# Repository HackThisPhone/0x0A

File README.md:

# 0x0A
The 0x0A Smartphone is an open-source, open-hardware smartphone. Repairable, customizable, and fully yours, the 0x0A phone gives the power back to you! 

## Features:

- Qualcomm Octa-Core ARM Cortex A-53 64-bit CPU @ 1.8GHz (2x quad-core with 512KB L2 cache)
- Adreno 506 GPU
- 16GB eMMC + 2GB LPDDR3
- 8,000mAh LiPo battery
- HD 720x1280 LCD with 16.7M color depth
- 10MP front & rear cameras
- 5G/4G/LTE/WCDMA
- WiFi 802.11a/b/g/n/ac
- Bluetooth 4.2/3.0/2.1
- GPS/BeiDou/GLONASS
- USB-C 3.0
- Dual SIM Standby
- 3D Printed Modular Case Design
- Full Schematics, BOM, & Supplier Info (self-serve on github)
- Android 9/10 Support
- Linux Support Planned (alternative operating systems welcomed here)

### Supported Carriers:

- North America    
  - Verizon
  - AT&T
  - T-Mobile
  - Sprint

Estimated BOM Cost: <$300
MSRP: $750

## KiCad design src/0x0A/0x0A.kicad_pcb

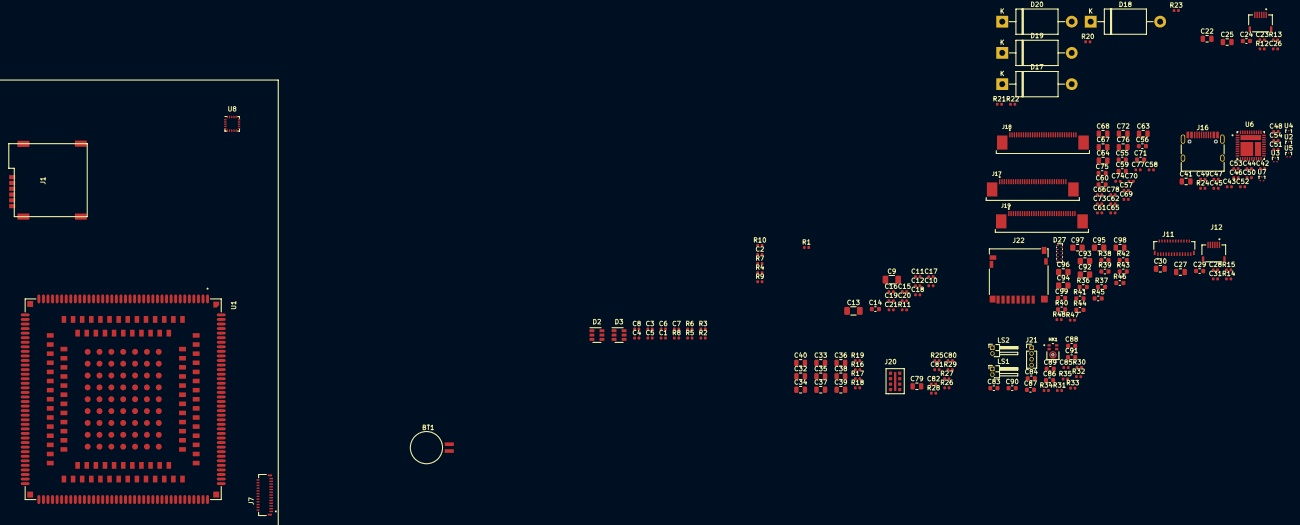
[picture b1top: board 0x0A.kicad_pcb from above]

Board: 2 copper layers, 179 parts (1 on the bottom side), 135 nets, no tracks yet.

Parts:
BT1: MS621FE-FL11E; BatteryHolder_Seiko_MS621F
C1, C2, C4, C5, C6, C8: 22pF; C_0402_1005Metric
C3, C7, C10, C15, C19, C23, C26, C28, C31, C42, C43, C44, C45, C46, C47, C48, C49, C50, C51, C52, C53, C54, C57, C58, C61, C62, C65, C66, C69, C70, C73, C74, C77, C78, C81, C82, C85: 100nF; C_0402_1005Metric
C9, C13: 100uF; C_1206_3216Metric
C11, C16, C17, C20: 33pF; C_0402_1005Metric
C12, C18, C21: 10pF; C_0402_1005Metric
C14, C55, C56, C59, C60, C71, C75: 1uF; C_0603_1608Metric
C22, C25, C27, C30, C41, C63, C64, C67, C68, C72, C76, C79, C98: 4.7uF; C_0805_2012Metric
C24, C29: 1nF; C_0603_1608Metric
C32, C33, C34, C35, C36, C37, C38, C39, C40: NP; C_0805_2012Metric
C80: 10nF; C_0402_1005Metric
C83, C84, C86, C87, C88, C89, C91, C99: 33pF; C_0603_1608Metric
C90: 100pF; C_0603_1608Metric
C92, C93, C94, C95, C96, C97: NP_27pF; C_0805_2012Metric_Pad1.15x1.40mm_HandSolder
D2, D3: ESDA6V1-5SC6; SOT-23-6
D17, D18, D19, D20: ?; D_DO-201AE_P15.24mm_Horizontal
D27: WE-TVS-824014881; UDFN-9_1.0x3.8mm_P0.5mm
J1, J2: SIM_Card; SIM-002-P6
J7, J11: FH26W-25S-0.3SHW(60); HRS_FH26W-25S-0.3SHW(60)
J8, J12: TF12S-6S-0.5SH(800); HRS_TF12S-6S-0.5SH(800)
J16: USB_C_Receptacle; USB_C_Receptacle_HRO_TYPE-C-31-M-12
J17, J18, J19: 3-1734839-0; TE_3-1734839-0
J20: STK3311 (WV|S34); STK3311
J21: Conn_01x04; PinHeader_1x04_P1.27mm_Vertical
J22: Micro_SD_Card_Det; microSD_HC_Hirose_DM3D-SF
LS1, LS2: Speaker; PinHeader_1x02_P1.27mm_Horizontal
MK1: MP23ABS1TR; MIC_MP23ABS1TR
R1, R16, R17, R18, R19, R30, R31, R32, R33, R34, R35, R48: 0R; R_0402_1005Metric
R2: 100k; R_0402_1005Metric
R3, R4, R5, R7, R8, R9: 22R; R_0402_1005Metric
R6, R10: 10k; R_0402_1005Metric
R11: 47k; R_0402_1005Metric
R12, R13, R14, R15: 2.2k; R_0402_1005Metric
R20, R21, R22: 1k; R_0402_1005Metric
R23, R24, R25: 10K; R_0402_1005Metric
R26, R28, R29: NP; R_0402_1005Metric
R27: OR; R_0402_1005Metric
R36, R37, R38, R39, R40, R41: 33R; R_0603_1608Metric
R42, R43, R44, R45, R46: NP; R_0603_1608Metric
R47: 120K; R_0402_1005Metric
U1: SC600YNAPAE53UGADA; XCVR_SC600YNAPAE53UGADA
U2, U3, U4, U5, U7: TPD2EUSB30; Texas_DRT-3
U6: PI3DBS12412A; CONV_MAX15035ETL+
U8: MPU-9250; InvenSense_QFN-24_3x3mm_P0.4mm

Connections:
/1.8V_GPIO: R2.1, U1.9
/1.8V_LCD: C24.1, C29.1, J7.19, J11.19, R12.1, R13.1, R14.1, R15.1, U1.10
/2.8V_SENSE: C25.1, C26.1, C30.1, C31.1, J8.1, J12.1, U1.11
/2.85V_LCD: C22.1, C23.1, C27.1, C28.1, J7.20, J11.20, U1.12
/ALS_INT_N: J20.2, R25.2, U1.177
/ANT_DRX: C33.2, R17.2, U1.149
/ANT_GNSS: C38.2, R19.2, U1.134
/ANT_MAIN: C32.2, R16.2, U1.19
/ANT_WIFI: C36.2, R18.2, U1.129
/BAT_PLUS: C9.1, C10.1, C11.1, C12.1, C13.1, C14.1, C16.1, U1.27, U1.36, U1.37, U1.38
/Cameras/AF_VDO: C67.1, C68.1, C69.1, C70.1, C76.1, C78.1, J17.2, J18.2, J19.2
/Cameras/AVDD: C63.1, C64.1, C65.1, C66.1, C72.1, C74.1, J17.7, J18.7, J19.7
/Cameras/DOVDD: C55.1, C56.1, C57.1, C58.1, C71.1, C73.1, J17.4, J18.4, J19.4
/Cameras/DVDD: C59.1, C60.1, C61.1, C62.1, C75.1, C77.1, J17.3, J18.3, J19.3
/DCAM_MCLK: J19.14, U1.194
/DCAM_PWDN: J19.12, U1.181
/DCAM_RESET: J19.11, U1.180
/EAR_N: C87.2, C88.1, LS1.2, U1.52
/EAR_P: C86.2, C87.1, LS1.1, U1.53
/FRONT_MCLK: J17.14, U1.100
/FRONT_PWDN: J17.12, U1.71
/FRONT_RESET: J17.11, U1.72
/FSYNC: R29.2, U1.237
/GYRO_INT: U1.178, U8.12
/LCD0_ID: J7.21, U1.153
/LCD0_TE: J7.18, U1.126
/LCD1_ID: J11.21, U1.151
/LCD1_RST: J11.17, U1.113
/LCD1_TE: J11.18, U1.114
/LCDO_RST: J7.17, U1.127
/LCD_BL_A: J7.24, J11.24, U1.21
/LCD_BL_K1: J7.23, U1.22
/LCD_BL_K2: J11.23, U1.23
/LDO12: R42.2, R43.2, R44.2, R45.2, R46.2, U1.179
/MIC1_N: J21.2, R30.2, R32.1, R32.2, U1.45
/MIC1_P: C84.1, J21.1, R31.1, R31.2, U1.44
/MIC3_P: C83.1, MK1.1, R33.1, R33.2, U1.169
/MIC_BIAS: C85.1, J21.3, MK1.5, R34.1, R34.2, U1.167
/PWR_KEY: R22.1, U1.39
/REAR_MCLK: J18.14, U1.99
/REAR_PWDN: J18.12, U1.73
/REAR_RESET: J18.11, U1.74
/SD_CLK: R37.2, U1.70
/SD_CMD: R40.2, U1.69
/SD_DATA0: R39.2, U1.68
/SD_DATA1: R41.2, U1.67
/SD_DATA2: R36.2, U1.66
/SD_DATA3: R38.2, U1.65
/SD_DET: D27.8, J22.9, J22.10, R47.1, U1.64
/SD_LD011: R48.2, U1.63
/SIM2_VDD: C7.2, D3.5, J2.1, R10.1, U1.210
/SIM_VDD: C3.2, D2.5, J1.1, R6.1, U1.141
/SPK_N: C90.2, C91.1, LS2.2, U1.54
/SPK_P: C89.2, C90.1, LS2.1, U1.55
/Sensors/LDO6_1V8: C80.1, R25.1, R28.1, U8.8, U8.22
/Sensors/LDO10_2V8: C81.1, J20.8, U8.13
/Sensors/SCL: J20.7, U8.23
/Sensors/SDA: J20.1, U8.24
/Sensors/VPH_PWR: C79.1, J20.5
/TP0_I2C_SCL: J8.6, R13.2, U1.140
/TP0_I2C_SDA: J8.5, R12.2, U1.206
/TP0_INT: J8.3, U1.139
/TP0_RST: J8.4, U1.138
/TP1_I2C_SCL: J12.6, R15.2, U1.205
/TP1_I2C_SDA: J12.5, R14.2, U1.204
/TP1_INT: J12.3, U1.137
/TP1_RST: J12.4, U1.136
/USB/RX+: C42.2, U6.4
/USB/RX-: C45.2, U6.5
/USB/RX_CON_1+: C49.2, U3.1
/USB/RX_CON_1-: C52.2, U3.2
/USB/RX_CON_2+: C53.2, U2.1
/USB/RX_CON_2-: C48.2, U2.2
/USB/TX+: C43.2, U6.1
/USB/TX-: C46.2, U6.2
/USB/TX_CON_1+: C51.2, U4.1
/USB/TX_CON_1-: C54.2, U4.2
/USB/TX_CON_2+: C47.2, U5.1
/USB/TX_CON_2-: C50.2, U5.2
/USB_CC1: J16.A5, U1.223
/USB_CC2: J16.B5, U1.224
/USB_D+: J16.A6, J16.B6, U1.32, U7.1
/USB_D-: J16.A7, J16.B7, U1.33, U7.2
/USB_SS_RX_M: C45.1, U1.172
/USB_SS_RX_P: C42.1, U1.171
/USB_SS_TX_M: C46.1, U1.175
/USB_SS_TX_P: C43.1, U1.174
/USIM1_CLK: R4.2, U1.143
/USIM1_DATA: R5.2, U1.142
/USIM1_DET: D2.6, J1.6, R2.2, U1.145
/USIM1_RST: R3.2, U1.144
/USIM2_CLK: R8.2, U1.208
/USIM2_DATA: R9.2, U1.209
/USIM2_RST: R7.2, U1.207
/VDD_RF: C19.1, C20.1, C21.1, U1.1, U1.2
/VOL_DOWN: R20.1, U1.147
/VOL_UP: R21.1, U1.146
/VPH_PWR: C15.1, C17.1, C18.1, U1.220, U1.221
/VRTC: BT1.1, U1.16
GND: BT1.2, C1.1, C2.1, C3.1, C4.2, C5.1, C6.1, C7.1, C8.2, C9.2, C10.2, C11.2, C12.2, C13.2, C14.2, C15.2, C16.2, C17.2, C18.2, C19.2, C20.2, C21.2, C22.2, C23.2, C24.2, C25.2, C26.2, C27.2, C28.2, C29.2, C30.2, C31.2, C32.1, C33.1, C34.1, C35.1, C36.1, C37.1, C38.1, C39.1, C41.1, C44.1, C55.2, C56.2, C57.2, C58.2, C59.2, C60.2, C61.2, C62.2, C63.2, C64.2, C65.2, C66.2, C67.2, C68.2, C69.2, C70.2, C71.2, C72.2, C73.2, C74.2, C75.2, C76.2, C77.2, C78.2, C79.2, C80.2, C81.2, C82.2, C83.2, C84.2, C85.2, C86.1, C88.2, C89.1, C91.2, C92.2, C93.2, C94.2, C95.2, C96.2, C97.2, C98.2, C99.2, D2.2, D3.2, D17.2, D18.2, D19.2, D20.2, D27.3, J1.5, J2.5, J7.1, J7.4, J7.7, J7.10, J7.13, J7.16, J7.S1, J7.S2, J8.2, J11.1, J11.4, J11.7, J11.10, J11.13, J11.16, J11.S1, J11.S2, J12.2, J16.A1, J16.A12, J16.B1, J16.B12, J16.S1, J17.6, J17.8, J17.13, J17.15, J17.18, J17.21, J17.24, J17.27, J17.30, J17.S1, J17.S2, J18.6, J18.8, J18.13, J18.15, J18.18, J18.21, J18.24, J18.27, J18.30, J18.S1, J18.S2, J19.6, J19.8, J19.13, J19.15, J19.18, J19.21, J19.24, J19.27, J19.30, J19.S1, J19.S2, J20.6, J21.4, J22.6, MK1.2, MK1.3, MK1.4, R1.2, R11.2, R24.1, R26.2, R27.1, R30.1, R35.1, R35.2, U1.3, U1.4, U1.18, U1.20, U1.28, U1.31, U1.34, U1.35, U1.40, U1.41, U1.42, U1.43, U1.47, U1.56, U1.62, U1.87, U1.98, U1.101, U1.112, U1.125, U1.128, U1.130, U1.133, U1.135, U1.148, U1.150, U1.154, U1.155, U1.156, U1.157, U1.158, U1.159, U1.163, U1.164, U1.165, U1.166, U1.168, U1.170, U1.173, U1.176, U1.182, U1.193, U1.195, U1.212, U1.213, U1.214, U1.218, U1.219, U1.222, U1.225, U1.235, U1.239, U1.240, U1.243, U1.245, U1.246, U1.247, U1.248, U1.249, U1.250, U1.251, U1.252, U1.253, U1.254, U1.255, U1.256, U1.257, U1.258, U1.259, U1.260, U1.261, U1.262, U1.263, U1.264, U1.265, U1.266, U1.267, U1.268, U1.269, U1.270, U1.271, U1.272, U1.273, U1.274, U1.275, U1.276, U1.277, U1.278, U1.279, U1.280, U1.281, U1.282, U1.283, U1.284, U1.285, U1.286, U1.287, U1.288, U1.289, U1.290, U1.291, U1.292, U1.293, U1.294, U1.295, U1.296, U1.297, U1.298, U1.299, U1.300, U1.301, U1.302, U1.303, U1.304, U1.305, U1.306, U1.307, U1.308, U1.309, U1.310, U1.311, U1.312, U1.313, U1.314, U1.315, U1.316, U1.317, U1.318, U1.319, U1.320, U1.321, U1.322, U1.323, U2.3, U3.3, U4.3, U5.3, U6.3, U6.12, U6.19, U7.3, U8.1, U8.18, U8.20
unnamed: C34.2, R16.1
unnamed: C35.2, R17.1
unnamed: C37.2, R18.1
unnamed: C1.2, D2.1, J1.7, R5.1, R6.2
unnamed: C2.2, D2.3, J1.3, R4.1
unnamed: C4.1, D2.4, J1.2, R3.1
unnamed: C5.2, D3.1, J2.7, R9.1, R10.2
unnamed: C6.2, D3.3, J2.3, R8.1
unnamed: C8.1, D3.4, J2.2, R7.1
unnamed: C39.2, C40.1, R19.1
unnamed: C41.2, C44.2, U6.7, U6.18
unnamed: C47.1, U6.16
unnamed: C48.1, U6.13
unnamed: C49.1, U6.9
unnamed: C50.1, U6.15
unnamed: C51.1, U6.11
unnamed: C52.1, U6.8
unnamed: C53.1, U6.14
unnamed: C54.1, U6.10
unnamed: C82.1, U8.10
unnamed: C92.1, D27.1, J22.1, R36.1, R42.1
unnamed: C93.1, D27.2, J22.2, R38.1, R43.1
unnamed: C94.1, D27.4, J22.3, R40.1, R44.1
unnamed: C95.1, D27.5, J22.5, R37.1
unnamed: C96.1, D27.6, J22.7, R39.1, R45.1
unnamed: C97.1, D27.7, J22.8, R41.1, R46.1
unnamed: C98.1, C99.1, D27.9, J22.4, R48.1
unnamed: D3.6, J2.6
unnamed: D17.1, R20.2
unnamed: D18.1, R21.2
unnamed: D19.1, R22.2
unnamed: J20.3, R26.1
unnamed: R27.2, R28.2, U8.9
unnamed: R29.1, U8.11
USB_VBUS: J16.A4, J16.A9, J16.B4, J16.B9, U1.162

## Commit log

2022-09-02 modified: README.md new file: src/0x0A/0x0A-cache.lib new file: src/0x0A/0x0A.kicad_pcb new file: src/0x0A/0x0A.pro new file: src/0x0A/0x0A.sch new file: src/0x0A/antenna.sch new file: src/0x0A/audio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
2022-09-02 modified: src/0x0A/0x0A-cache.lib modified: src/0x0A/0x0A.sch modified: src/0x0A/antenna.sch modified: src/0x0A/audio.sch modified: src/0x0A/buttons.sch modified: src/0x0A/display.sch modified: src/0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
2022-09-02 new file: imgs/better.png modified: src/0x0A/0x0A-cache.lib modified: src/0x0A/0x0A.sch modified: src/0x0A/antenna.sch modified: src/0x0A/audio.sch modified: src/0x0A/buttons.sch new file: src/0x0A/c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
    Added 3D models, integrated front & rear cameras, flash light, reformatting & more
2022-09-04 Updated schematics, started working on board layout
2022-09-04 new file: docs/schematics.pdf modified: src/0x0A/0x0A.pro Added schematics pdf file
